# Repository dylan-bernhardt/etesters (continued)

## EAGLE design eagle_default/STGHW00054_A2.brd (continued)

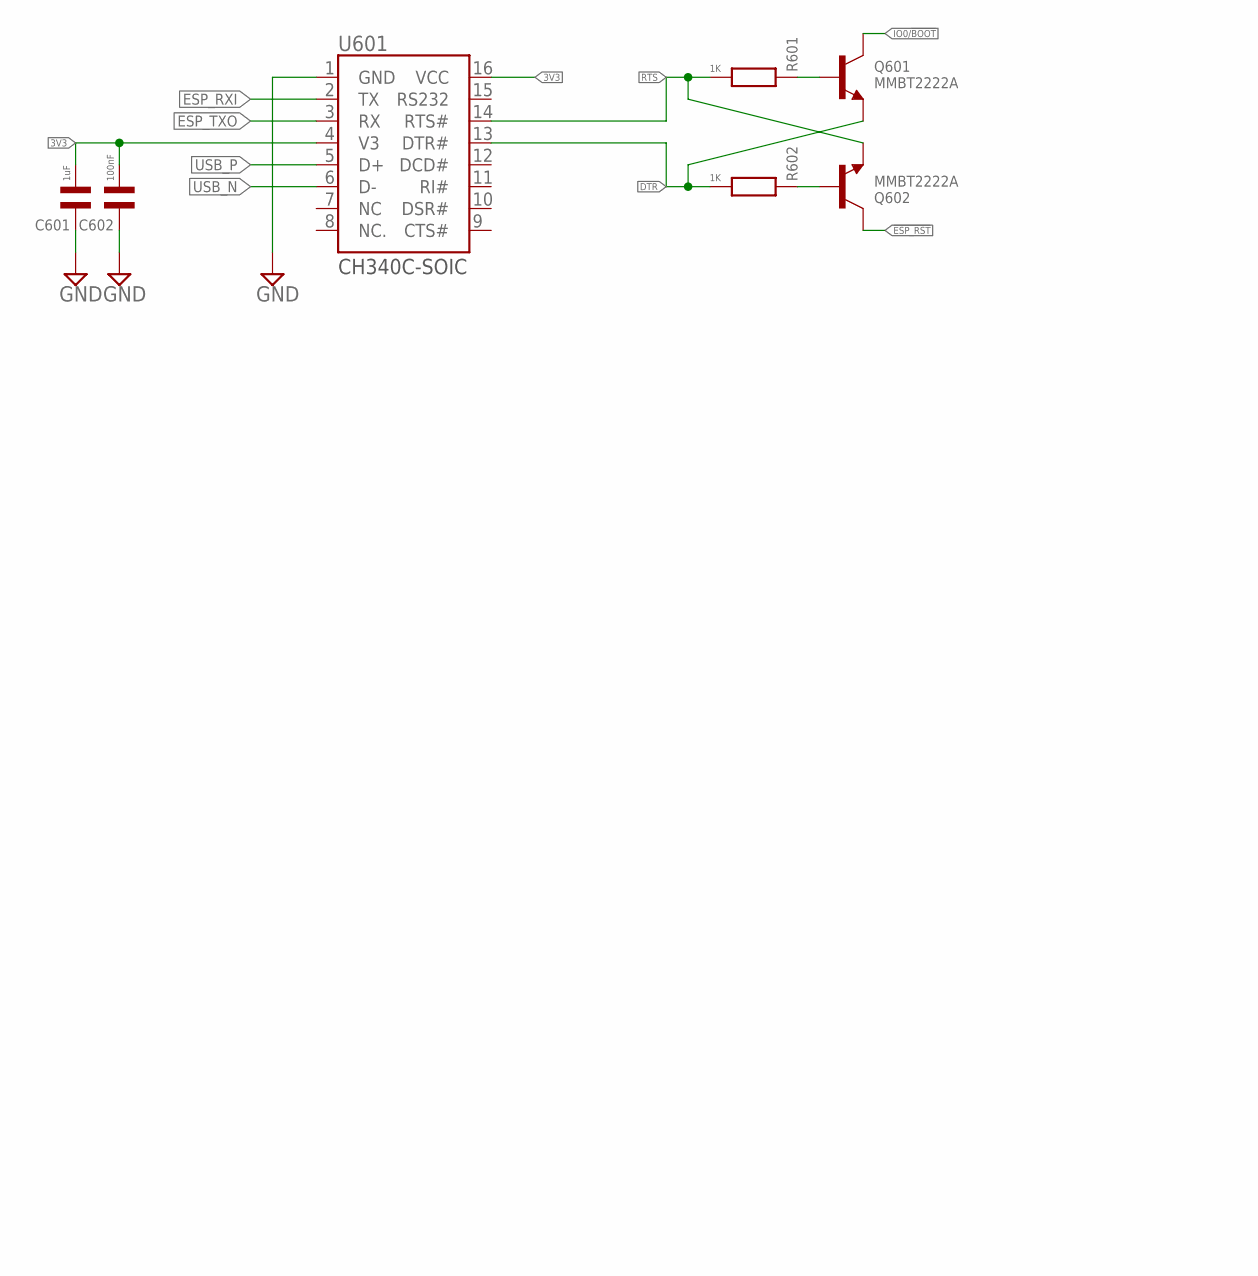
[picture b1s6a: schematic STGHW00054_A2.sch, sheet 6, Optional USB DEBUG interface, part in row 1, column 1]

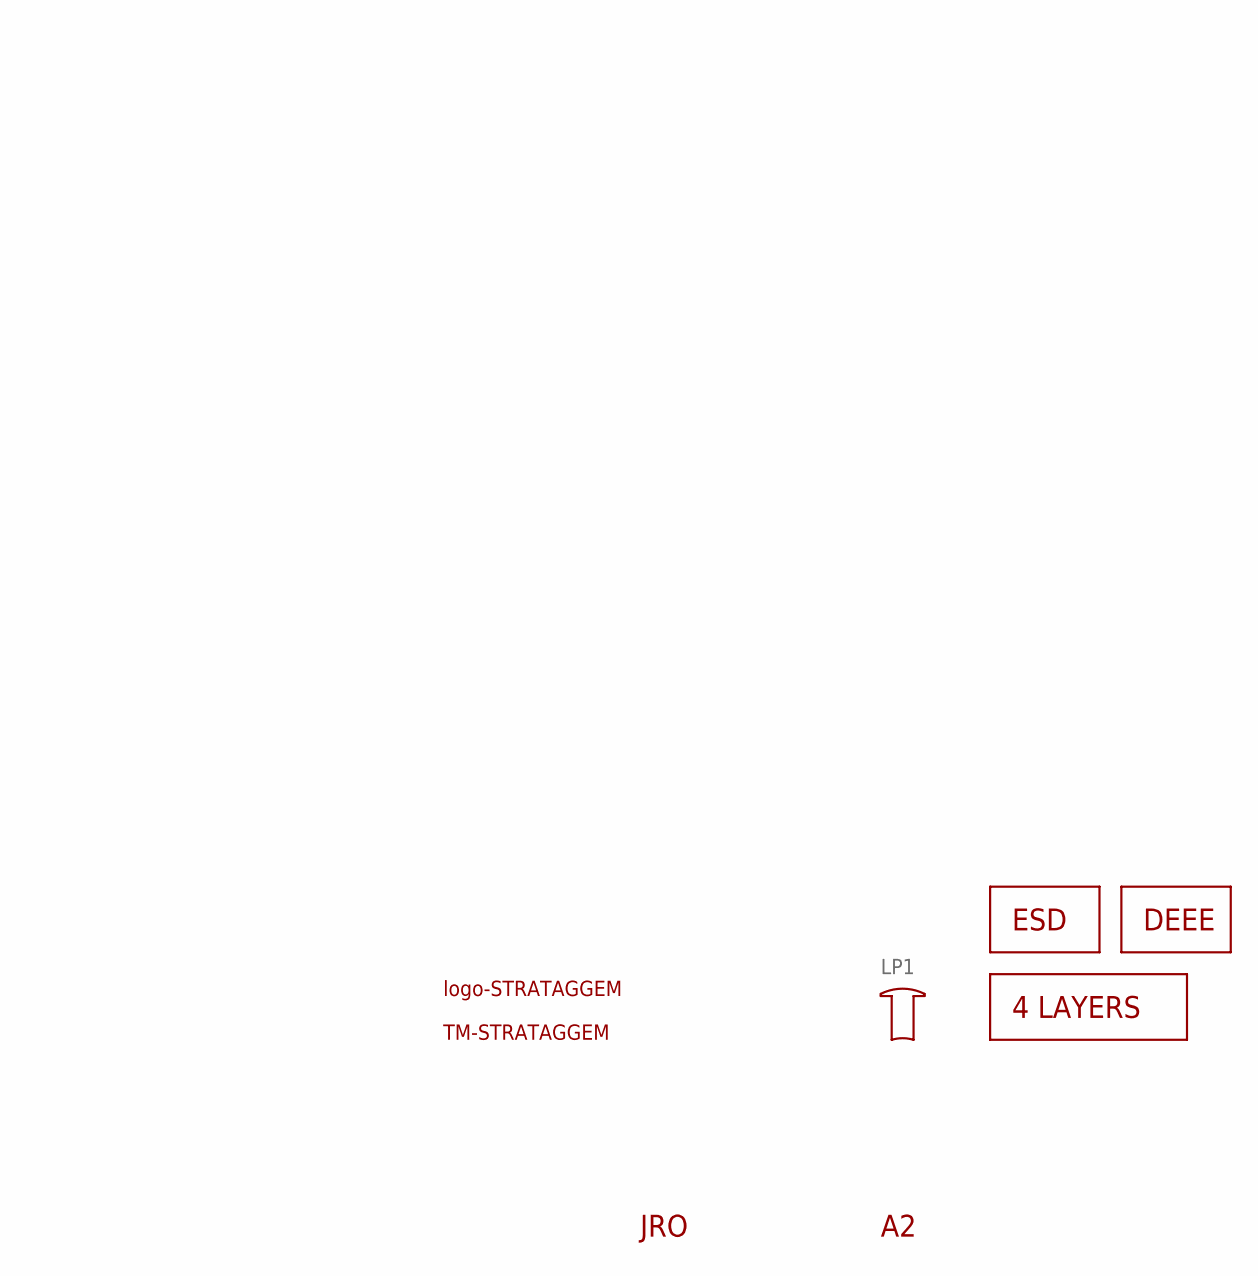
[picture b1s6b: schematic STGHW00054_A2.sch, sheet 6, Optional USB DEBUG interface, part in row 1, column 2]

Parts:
C601: 1uF; C0603; MPN CL10B105KP8NNNC
C602: 100nF; C0603; MPN CL10B104KO8NNNC
LOGO1: LOGO_STRATAGGEM_SILK_5; STG_LOGO_1L_SILK_5
LOGO601: ESD_LOGO-SILK-TOP-5; ESD_TOP_5MM
LOGO602: DEEE_LOGO-SILK-TOP-5; DEEE_MUELLTONNE_TOP_5MM
LP1: SLP3-150-250-F
Q601, Q602: MMBT2222A; SOT23-WIDE; MPN MMBT2222A
R601, R602: 1K; R0603; MPN WR06X1001FTL
SPEC1: LAYER_4; 4LAYER
TM1: TM_STRATAGGEM_SILK_20; STG_MARK_SILK_TOP_20MM
U601: CH340C-SOIC; SOIC127P600X175-16

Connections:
3V3: C601.2, C602.2, U601.4 (V3), U601.16 (VCC); also elsewhere on the board
!ESP_RST!: Q602.3 (C); also elsewhere on the board
DTR: Q601.2 (E), R602.2, U601.13 (DTR#)
ESP_RXI: U601.2 (TX); also elsewhere on the board
ESP_TXO: U601.3 (RX); also elsewhere on the board
GND: C601.1, C602.1, U601.1 (GND); also elsewhere on the board
IO0/!BOOT!: Q601.3 (C); also elsewhere on the board
unnamed: Q601.1 (B), R601.1
unnamed: Q602.1 (B), R602.1
RTS: Q602.2 (E), R601.2, U601.14 (RTS#)
USB_N: U601.6 (D-); also elsewhere on the board
USB_P: U601.5 (D+); also elsewhere on the board

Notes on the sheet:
JRO

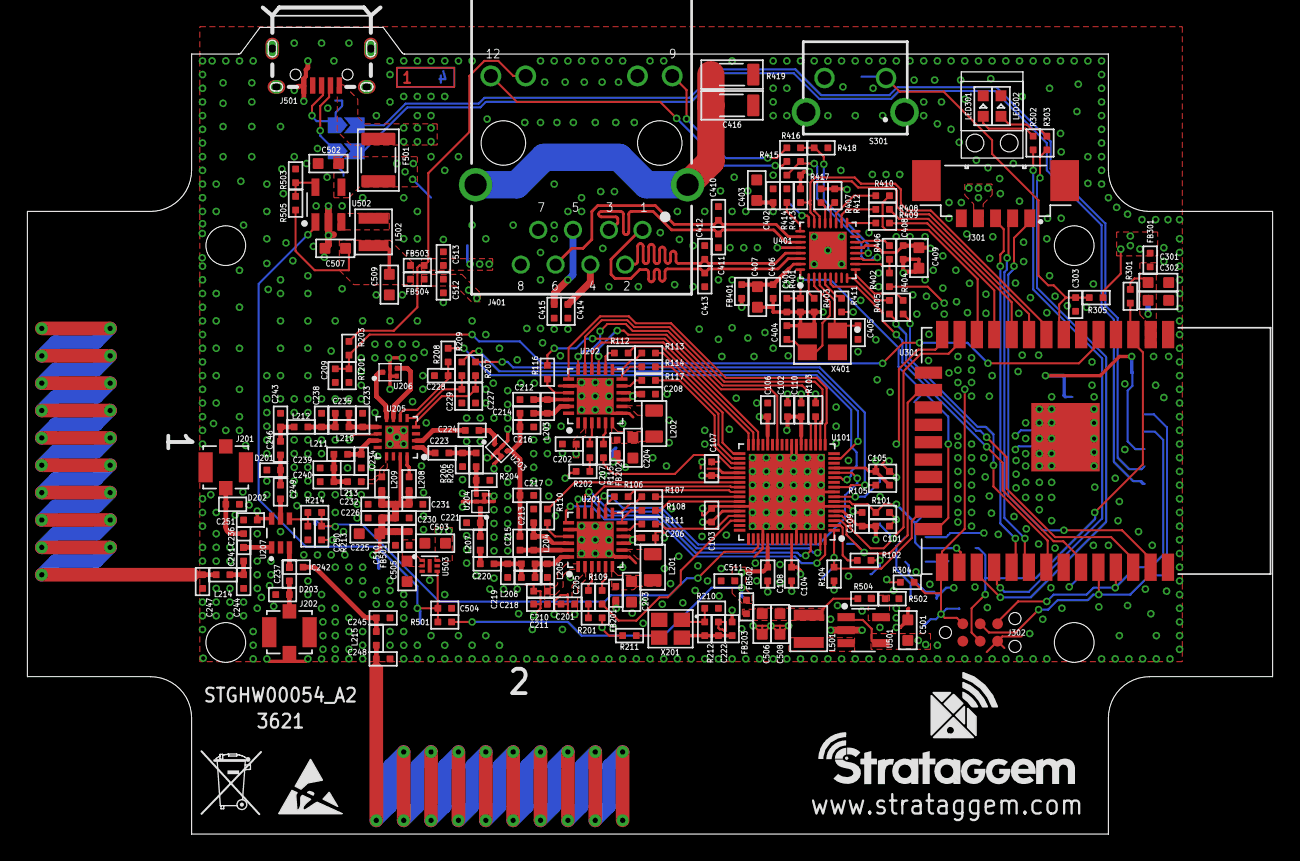
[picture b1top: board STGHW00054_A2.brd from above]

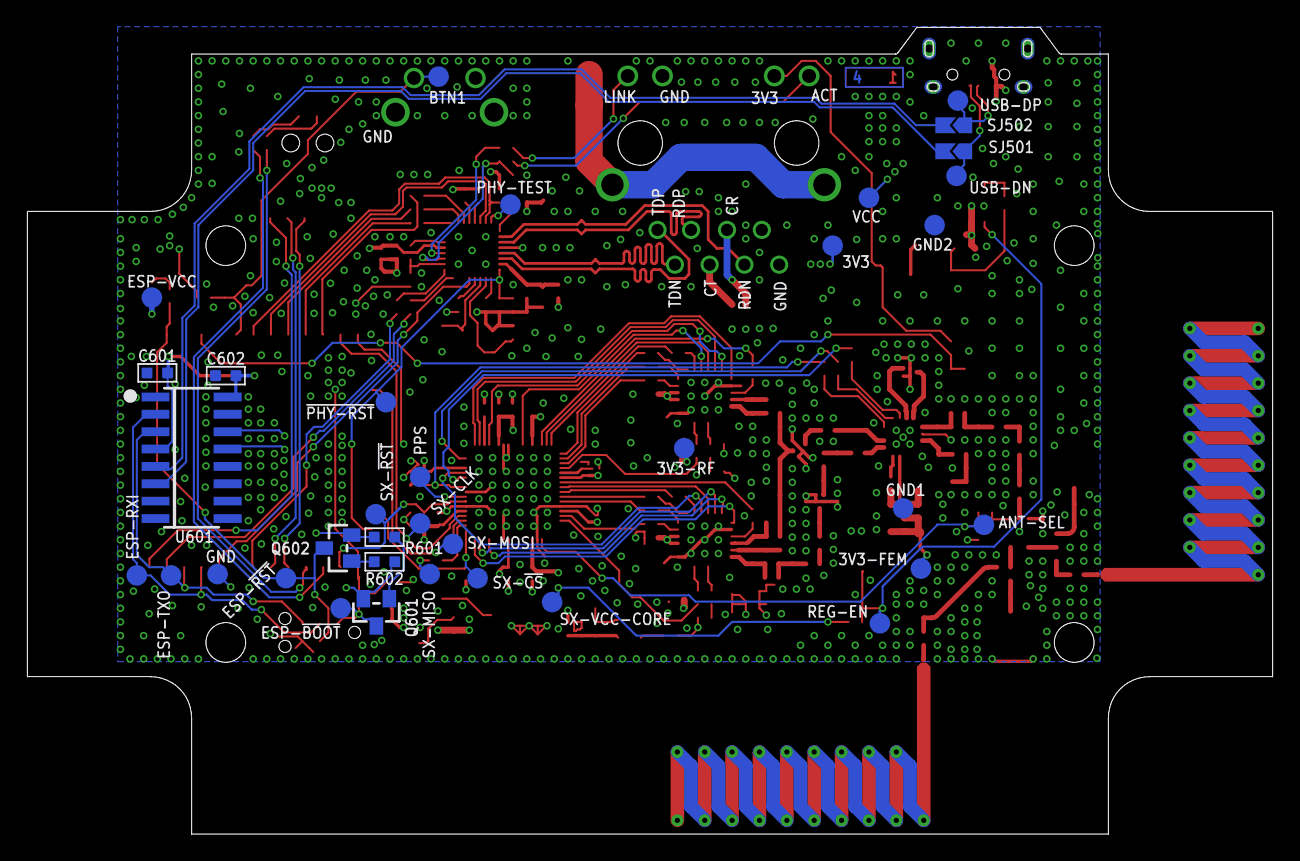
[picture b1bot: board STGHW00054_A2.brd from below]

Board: 4 copper layers, 91.0 x 59.0 mm, 252 parts (35 on the bottom side), 170 nets.

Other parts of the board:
U$1: PFF10-4-7(OUTLINE)

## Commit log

2023-01-20 ajout du projet
2023-01-20 un bouton pour télécharger tous les fichiers / ajout du .gitignore
2023-01-20 ajout d'une interface pour choisir où enregistrer les fichiers
2023-01-20 création du __init__.py / modifications qui contribuent au bon fonctionnement du module
2023-01-20 ajout d'une fonctionnalité permettant d'empecher de lancer une étape tant que la précédente n'est pas validée
2023-01-20 cleaning / ajout de la demande pour centre la carte avec le repère
2023-01-20 Correction de bugs et d'erreurs pour les étapes 1 et 2
2023-01-20 Ajout d'une fonction pour cocher certains boutons
2023-01-23 Fonctionnaliré permettant de ne pas pouvoir lancer une étape tant que la précédente n'est pas validée
2023-01-23 Ajout d'une étape permettant à l'utilisateur de choisir la dimension du pcb contenant uniquement les testpoints
2023-01-23 Changement du bg pour les labels de l'étape pour le choix des dimensions
2023-01-23 Creation du fichier .toml pour initialiser poetry
2023-01-23 Correction d'un bug lorsqu'on refusait de rejouer une étape
2023-01-23 ajout du .lock
2023-01-23 ajout des dependencies
2023-01-23 ajout du fichier correspondant à la création automatique de la doc
2023-01-23 Write documentation for menu & download_files
2023-01-24 ajout de documentation (il reste create_eagle_files à terminer)
2023-01-24 Correction de bugs / ajout de la doc / précision de la création des fichiers
2023-01-25 Ajout d'options sur le schéma de la carte (légende/sélectionner tout/valider/repère)
2023-01-25 Le fichier où les nouveaux fichiers sont enregistrés et maintenant ouvert à la fermeture de l'application
2023-01-25 Suppression de fichiers inutiles
2023-01-25 différenciation des précisions x et y pour les fichiers gerber
2023-01-26 Mise en place d'étapes permettant de séléctionner les trous du fichiers excellon à garder
2023-01-26 ajout de la doc
2023-01-26 modif du read-me
2023-01-26 Résolution de pb lorsqu'on veut refaire certaines étapes
2023-01-26 Correction erreur lorsqu'on cancel le dl
2023-01-26 précision d'element en doc
2023-01-27 suppression d'un print
2023-01-27 réorganisation des fichiers, ajout d'un exemple
2023-01-27 fonction pour éclaircir une couleur permettant à l'utilisateur de changer la couleur de la gui + update doc
